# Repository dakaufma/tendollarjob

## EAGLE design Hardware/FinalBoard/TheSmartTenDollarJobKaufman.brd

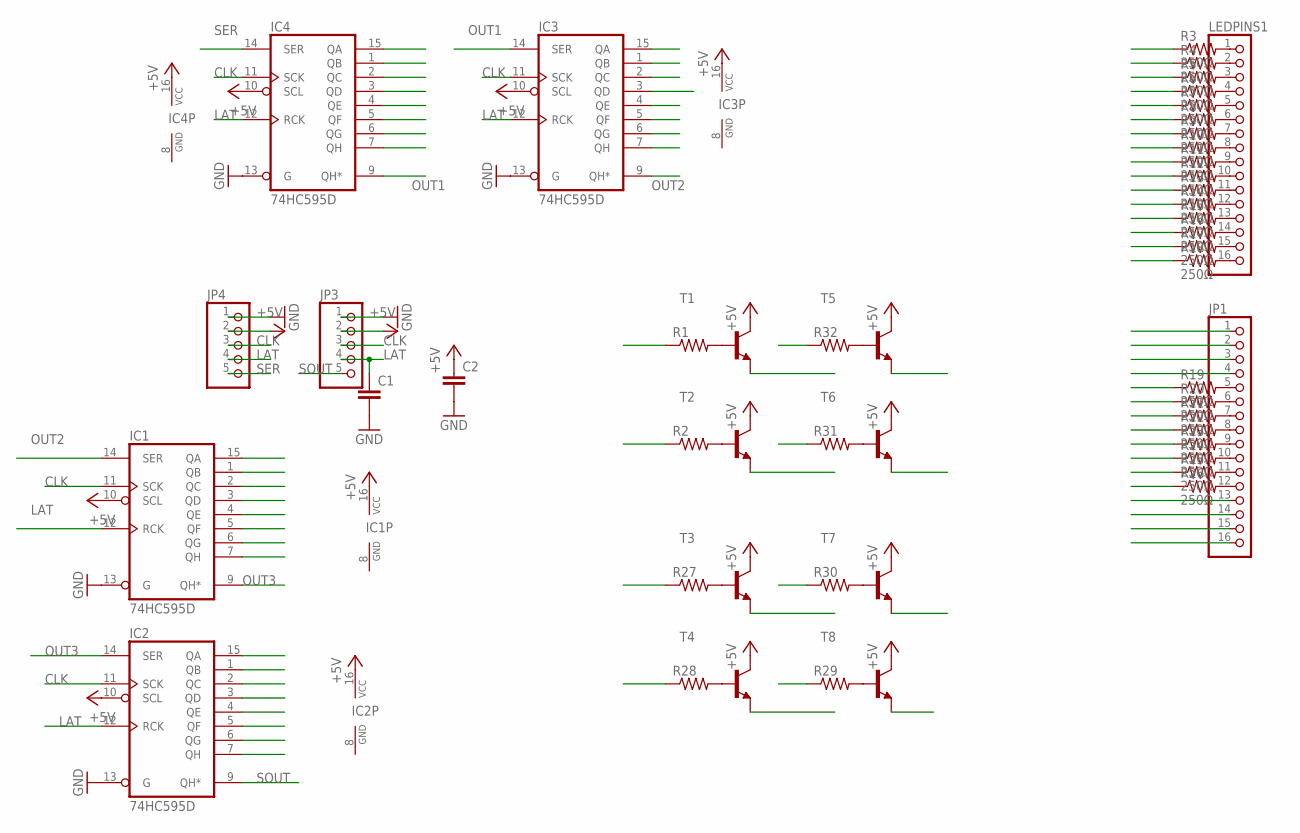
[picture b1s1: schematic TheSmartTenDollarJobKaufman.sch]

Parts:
C1, C2: C-EUC0603; C0603
IC1, IC2, IC3, IC4: 74HC595D; SO16
JP1: PINHD-1X16; 1X16
JP3, JP4: PINHD-1X5; 1X05
LEDPINS1: PINHD-1X16; 1X16
R1, R2, R27, R28, R29, R30, R31, R32: R-US_R0603; R0603
R3, R4, R5, R6, R7, R8, R9, R10, R11, R12, R13, R14, R15, R16, R17, R18, R19, R20, R21, R22, R23, R24, R25, R26: 250Ω; R0603
T1, T2, T3, T4, T5, T6, T7, T8: -NPN-SOT23-CBE; SOT23-EBC

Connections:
+5V: C2.1, IC1.10 (SCL), IC1.16 (VCC), IC2.10 (SCL), IC2.16 (VCC), IC3.10 (SCL), IC3.16 (VCC), IC4.10 (SCL), IC4.16 (VCC), JP3.2, JP4.2, T1.C, T2.C, T3.C, T4.C, T5.C, T6.C, T7.C, T8.C
CLK: IC1.11 (SCK), IC2.11 (SCK), IC3.11 (SCK), IC4.11 (SCK), JP3.3, JP4.3
GND: C1.2, C2.2, IC1.8 (GND), IC1.13 (G), IC2.8 (GND), IC2.13 (G), IC3.8 (GND), IC3.13 (G), IC4.8 (GND), IC4.13 (G), JP3.1, JP4.1
LAT: C1.1, IC1.12 (RCK), IC2.12 (RCK), IC3.12 (RCK), IC4.12 (RCK), JP3.4, JP4.4
unnamed: IC3.15 (QA), R3.1
unnamed: IC3.7 (QH), R4.1
unnamed: IC3.6 (QG), R5.1
unnamed: IC3.5 (QF), R6.1
unnamed: IC3.4 (QE), R7.1
unnamed: IC3.3 (QD), R8.1
unnamed: IC3.2 (QC), R9.1
unnamed: IC3.1 (QB), R10.1
unnamed: IC4.7 (QH), R11.1
unnamed: IC4.6 (QG), R12.1
unnamed: IC4.5 (QF), R13.1
unnamed: IC4.4 (QE), R14.1
unnamed: IC4.3 (QD), R15.1
unnamed: IC4.2 (QC), R16.1
unnamed: IC4.1 (QB), R17.1
unnamed: IC4.15 (QA), R18.1
unnamed: JP1.1, T1.B (E)
unnamed: JP1.2, T2.B (E)
unnamed: JP1.3, T3.B (E)
unnamed: JP1.4, T4.B (E)
unnamed: IC1.4 (QE), R19.1
unnamed: IC1.5 (QF), R20.1
unnamed: IC1.6 (QG), R21.1
unnamed: IC1.7 (QH), R22.1
unnamed: IC2.1 (QB), R23.1
unnamed: IC2.2 (QC), R24.1
unnamed: IC2.3 (QD), R25.1
unnamed: IC2.4 (QE), R26.1
unnamed: JP1.13, T5.B (E)
unnamed: JP1.14, T6.B (E)
unnamed: JP1.15, T7.B (E)
unnamed: JP1.16, T8.B (E)
unnamed: LEDPINS1.1, R3.2
unnamed: R1.2, T1.E (B)
unnamed: LEDPINS1.2, R4.2
unnamed: LEDPINS1.3, R5.2
unnamed: LEDPINS1.4, R6.2
unnamed: LEDPINS1.5, R7.2
unnamed: LEDPINS1.6, R8.2
unnamed: LEDPINS1.7, R9.2
unnamed: LEDPINS1.8, R10.2
unnamed: LEDPINS1.9, R11.2
unnamed: LEDPINS1.10, R12.2
unnamed: LEDPINS1.11, R13.2
unnamed: LEDPINS1.12, R14.2
unnamed: LEDPINS1.13, R15.2
unnamed: LEDPINS1.14, R16.2
unnamed: LEDPINS1.15, R17.2
unnamed: LEDPINS1.16, R18.2
unnamed: JP1.5, R19.2
unnamed: JP1.6, R20.2
unnamed: JP1.7, R21.2
unnamed: JP1.8, R22.2
unnamed: JP1.9, R23.2
unnamed: JP1.10, R24.2
unnamed: JP1.11, R25.2
unnamed: JP1.12, R26.2
unnamed: R2.2, T2.E (B)
unnamed: R27.2, T3.E (B)
unnamed: R28.2, T4.E (B)
unnamed: R29.2, T8.E (B)
unnamed: R30.2, T7.E (B)
unnamed: R31.2, T6.E (B)
unnamed: R32.2, T5.E (B)
OUT1: IC3.14 (SER), IC4.9 (QH*)
OUT2: IC1.14 (SER), IC3.9 (QH*)
OUT3: IC1.9 (QH*), IC2.14 (SER)
QA: IC1.15 (QA), R1.1
QB: IC1.1 (QB), R2.1
QC: IC1.2 (QC), R27.1
QD: IC1.3 (QD), R28.1
QE: IC2.5 (QF), R32.1
QF: IC2.6 (QG), R31.1
QG: IC2.7 (QH), R30.1
QH: IC2.15 (QA), R29.1
SER: IC4.14 (SER), JP4.5
SOUT: IC2.9 (QH*), JP3.5

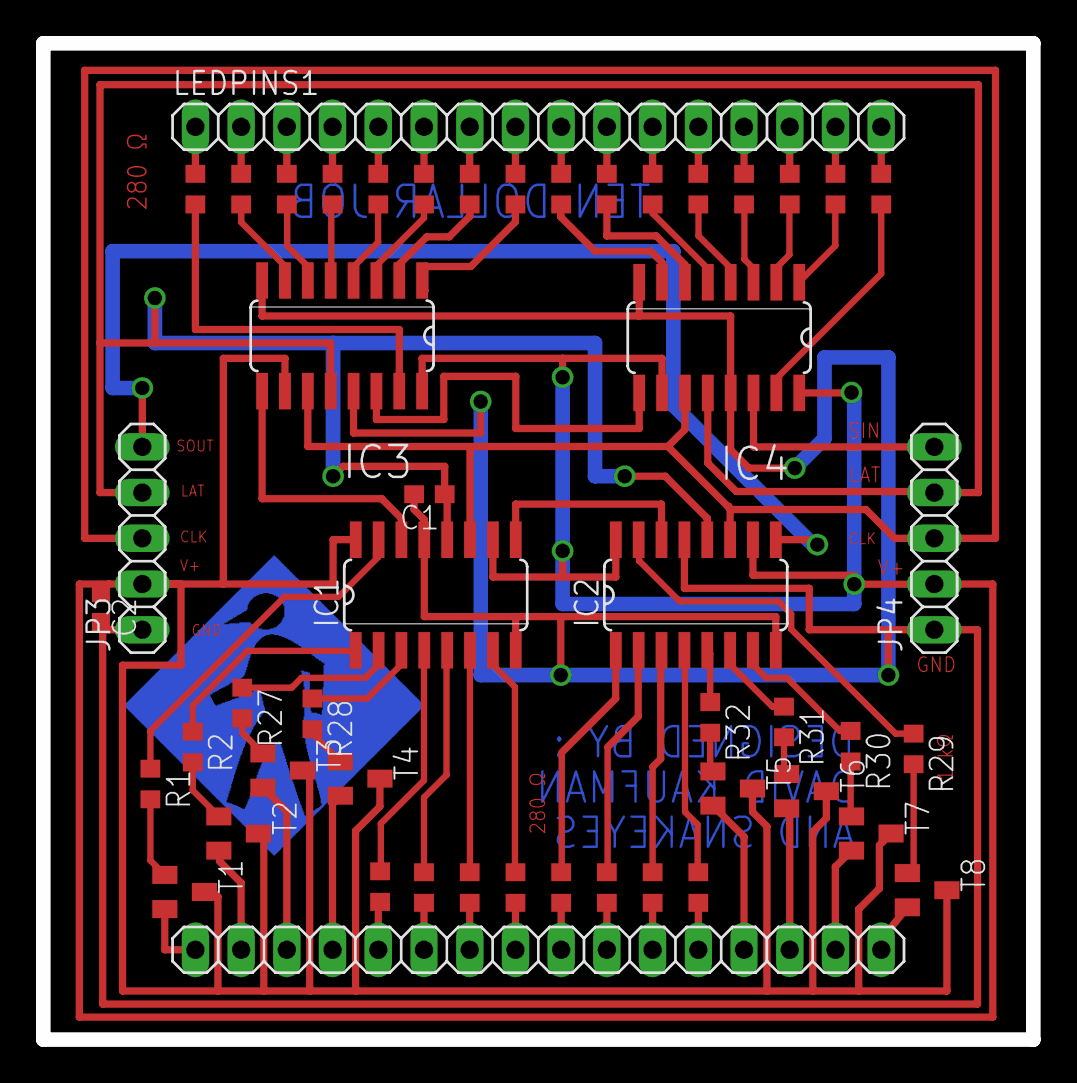
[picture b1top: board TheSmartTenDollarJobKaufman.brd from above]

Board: 2 copper layers, 55.0 x 55.4 mm, 50 parts (0 on the bottom side), 81 nets.

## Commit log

2013-07-23 Board and Eagle schmatics
2013-07-26 Wrote and tested an arduino controller for the matrix.
    Current code just displays all white, but functionality exists for
    displaying anything and we think it works.
2013-07-31 Update ArduinoDisplayController.ino
    Change the pinorder to reflect the pin order on the prototype soldered board
2013-08-01 Update ArduinoDisplayController.ino
    I had my pinorder reversed
2013-08-01 Latest Boards. Larger Vias and Collector line wired together
2013-08-01 Added CAM:
2013-08-02 Image of 6 boards, hopefully aligned so we can fold them.
2013-08-03 Updated the CAD. The shift registers need to be spaced out and the trasistors need to be flipped
2013-08-03 Add MITERS DRC
2013-08-03 Awwwwww yeahhhhhhhh. Final board design.
2013-08-03 Updated board images.
2013-08-05 Updated board, added pecker logo.
2013-08-05 Refactored stuff.
2013-08-06 Started scrolling-text app
2013-08-07 MORE COPPER!
2013-08-07 MOAR COPPER
2013-08-08 Final boards file -- includes more copper this time and is spaced out better
